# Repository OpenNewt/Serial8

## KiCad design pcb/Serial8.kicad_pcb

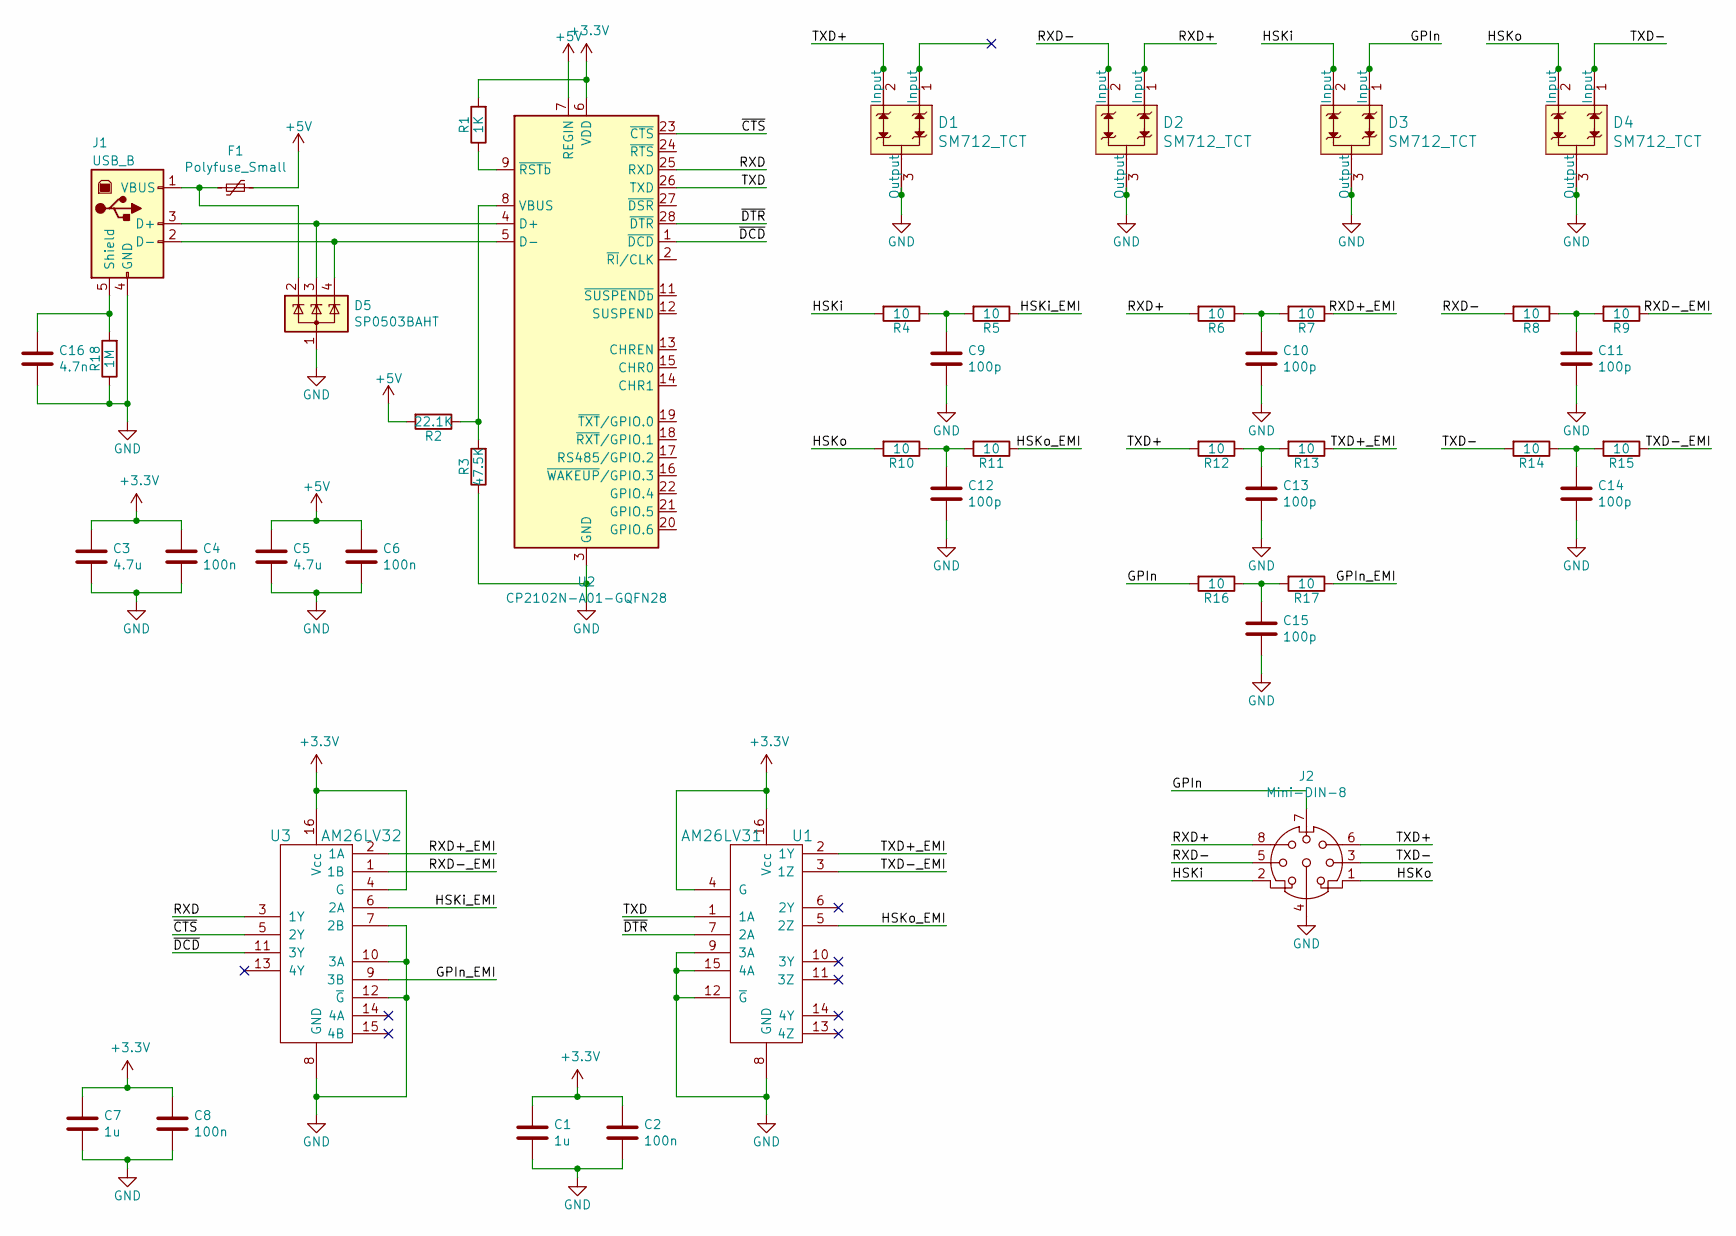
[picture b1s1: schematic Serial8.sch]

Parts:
C1, C7: 1u; C_0603
C2, C4, C6, C8: 100n; C_0603
C3, C5: 4.7u; C_0805
C9, C10, C11, C12, C13, C14, C15: 100p; C_0603
C16: 4.7n; C_0603
D1, D2, D3, D4: SM712_TCT; SOT-23-3; MPN SM712.TCT; Digi-Key_PN SM712CT-ND
D5: SP0503BAHT; SOT-143
F1: Polyfuse_Small; Fuse_1206_3216Metric
J1: USB_B
J2: Mini-DIN-8
R1: 1K; R_0603
R2: 22.1K; R_0603
R3: 47.5K; R_0603
R4, R5, R6, R7, R8, R9, R10, R11, R12, R13, R14, R15, R16, R17: 10; R_0603
R18: 1M; R_0603
U1: AM26LV31; SOIC-16_3.9x9.9mm_Pitch1.27mm; PartNumber 296-1010-1-ND
U2: CP2102N-A01-GQFN28; QFN-28-1EP_5x5mm_P0.5mm_EP3.35x3.35mm
U3: AM26LV32; SOIC-16_3.9x9.9mm_Pitch1.27mm; PartNumber 296-1011-1-ND

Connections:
+3V3: C1.1, C2.1, C3.1, C4.1, C7.1, C8.1, R1.2, U1.4 (G), U1.16 (Vcc), U2.6 (VDD), U3.4 (G), U3.16 (Vcc)
+5V: C5.1, C6.1, F1.1, R2.2, U2.7 (REGIN)
/GPIn: D3.1 (Input), J2.7, R16.2
/GPIn_EMI: R17.1, U3.9 (3B)
/HSKi: D3.2 (Input), J2.2, R4.2
/HSKi_EMI: R5.1, U3.6 (2A)
/HSKo: D4.2 (Input), J2.1, R10.2
/HSKo_EMI: R11.1, U1.5 (2Z)
/RXD: U2.25 (RXD), U3.3 (1Y)
/RXD+: D2.1 (Input), J2.8, R6.2
/RXD+_EMI: R7.1, U3.2 (1A)
/RXD-: D2.2 (Input), J2.5, R8.2
/RXD-_EMI: R9.1, U3.1 (1B)
/TXD: U1.1 (1A), U2.26 (TXD)
/TXD+: D1.2 (Input), J2.6, R12.2
/TXD+_EMI: R13.1, U1.2 (1Y)
/TXD-: D4.1 (Input), J2.3, R14.2
/TXD-_EMI: R15.1, U1.3 (1Z)
/~CTS: U2.23 (~CTS), U3.5 (2Y)
/~DCD: U2.1 (~DCD), U3.11 (3Y)
/~DTR: U1.7 (2A), U2.28 (~DTR)
GND: C1.2, C2.2, C3.2, C4.2, C5.2, C6.2, C7.2, C8.2, C9.2, C10.2, C11.2, C12.2, C13.2, C14.2, C15.2, C16.2, D1.3 (Output), D2.3 (Output), D3.3 (Output), D4.3 (Output), D5.1 (A), J1.4 (GND), J2.4, R3.1, R18.1, U1.8 (GND), U1.9 (3A), U1.12 (~G), U1.15 (4A), U2.3 (GND), U2.29 (GND), U3.7 (2B), U3.8 (GND), U3.10 (3A), U3.12 (~G)
unnamed: C9.1, R4.1, R5.2
unnamed: C10.1, R6.1, R7.2
unnamed: C11.1, R8.1, R9.2
unnamed: C12.1, R10.1, R11.2
unnamed: C13.1, R12.1, R13.2
unnamed: C14.1, R14.1, R15.2
unnamed: C15.1, R16.1, R17.2
unnamed: C16.1, J1.5 (Shield), R18.2
unnamed: D5.2 (K), F1.2, J1.1 (VBUS)
unnamed: D5.3 (K), J1.3 (D+), U2.4 (D+)
unnamed: D5.4 (K), J1.2 (D-), U2.5 (D-)
unnamed: R1.1, U2.9 (~RSTb)
unnamed: R2.1, R3.2, U2.8 (VBUS)

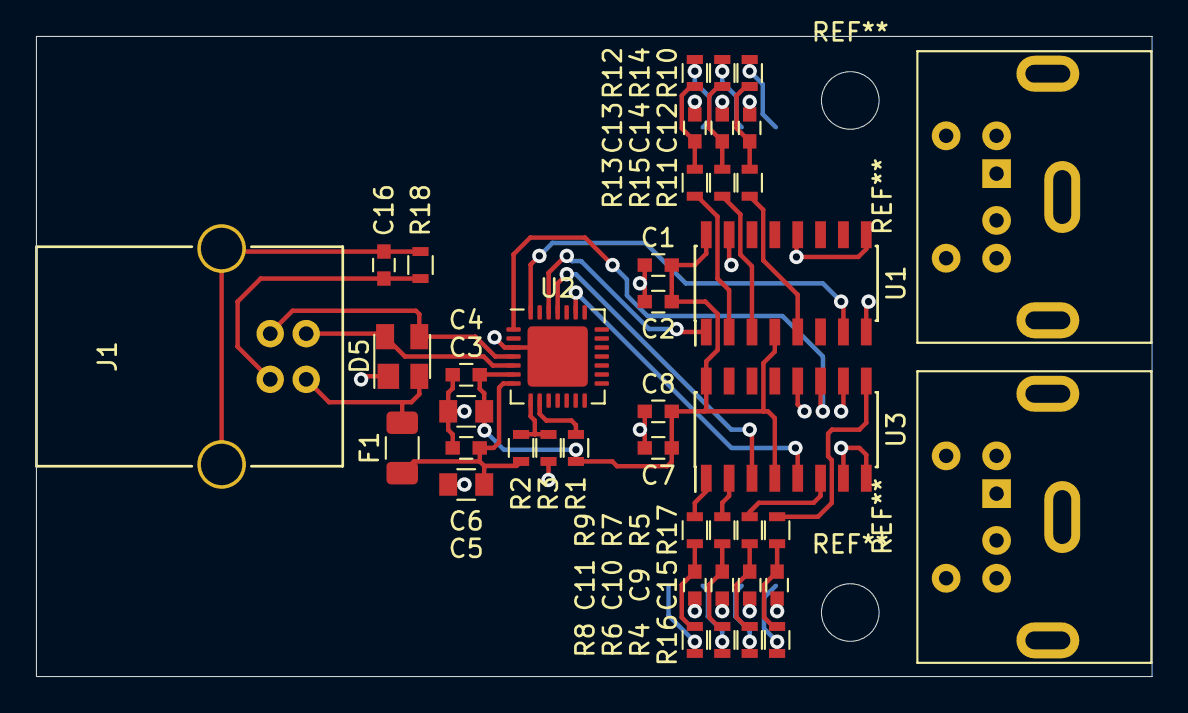
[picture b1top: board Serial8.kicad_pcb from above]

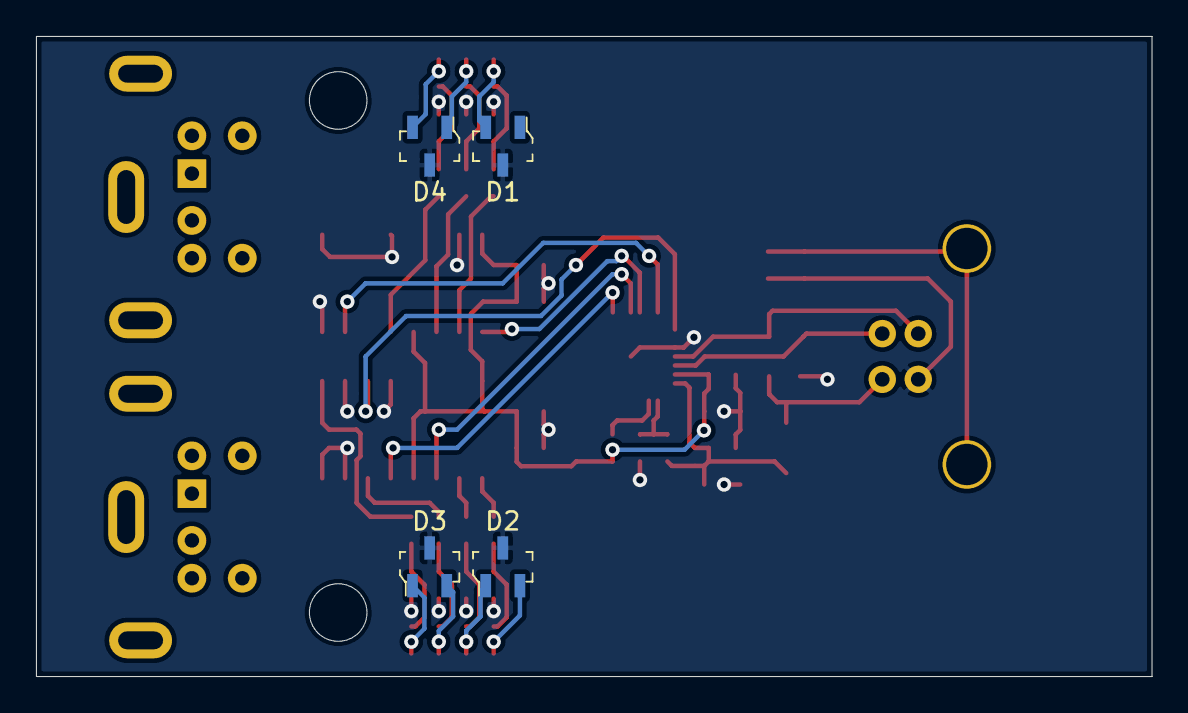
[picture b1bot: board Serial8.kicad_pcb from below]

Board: 2 copper layers, 62.0 x 35.6 mm, 44 parts (4 on the bottom side), 35 nets.

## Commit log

2020-06-20 Almost finished layout... but probably need some massive change to make it small enough
2020-06-20 Rearranged EMI filters and ESD diodes. Board is about 16mm shorter now.
    Need to make a MiniDIN8 footprint, and reduce to 1 connector - 2 were in place to cover the ADB version of this PCB (same mounting holes, USB placement, and board size; different DIN count and locati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
